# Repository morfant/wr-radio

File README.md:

# WR-Radio

## 설정 방법

### 1. 첫 실행
```bash
python3 wr-radio.py
```
첫 실행 시 `config.json` 파일이 자동 생성됩니다.

### 2. 스테이션 추가/변경
```bash
nano ~/wr-radio/config.json
```
```json
{
  "stations": [
    {
      "name": "내가 좋아하는 라디오",
      "url": "http://stream-url.mp3",
      "location": "Seoul, Korea",
      "lat": 37.5665,
      "lon": 126.9780,
      "color": [255, 100, 100]
    }
  ]
}
```

### 3. 날씨 기능 (선택)
1. https://openweathermap.org/appid 에서 무료 API 키 발급
2. `config.json`에 키 입력:
```json
   {
     "openweather_api_key": "여기에_키_입력"
   }
```

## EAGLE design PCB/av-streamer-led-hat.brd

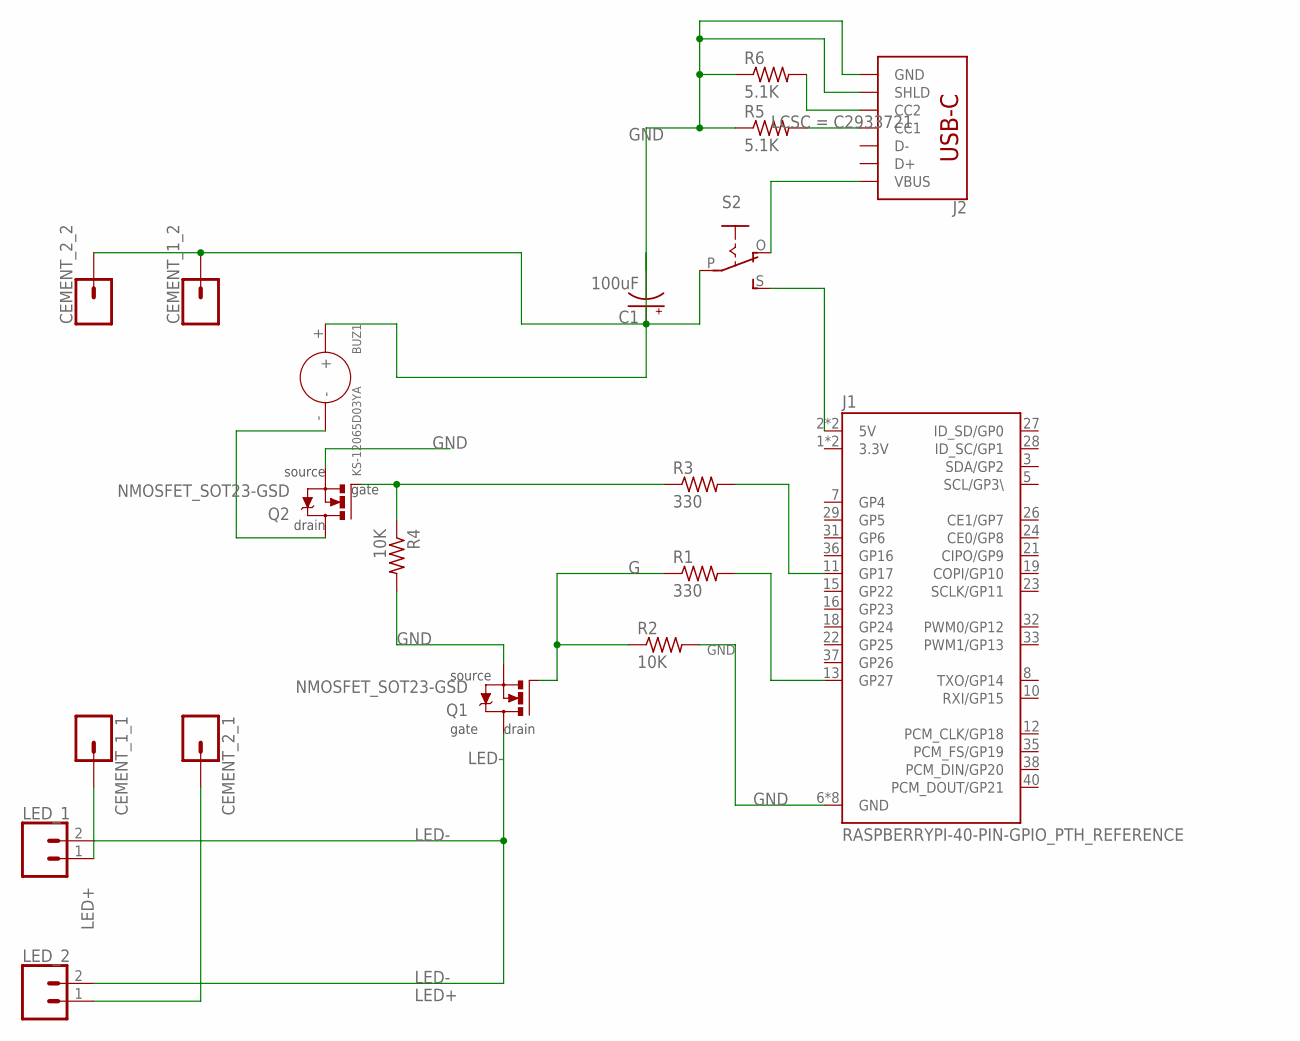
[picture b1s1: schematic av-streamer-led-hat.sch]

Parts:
BUZ1: KS-12065D03YA; BZ2-7.6-D12.0XH6.5MM
C1: 100uF; CPOL-RADIAL-2.5MM-6.5MM
CEMENT_1_1, CEMENT_1_2, CEMENT_2_1, CEMENT_2_2: CONN_01; 1X01
J1: RASPBERRYPI-40-PIN-GPIO_PTH_REFERENCE; RASPBERRY_PI_HAT_40_PIN_PTH_WITH_REFERNCE
J2: USB_C_2-LAYER_PADS; USB-C-16P-2LAYER-PADS
LED_1, LED_2: CONN_02; 1X02
Q1: NMOSFET_SOT23-GSD; SOT23; LCSC C181090
Q2: NMOSFET_SOT23-GSD; SOT23
R1, R3: 330; R1206
R2, R4: 10K; R1206
R5, R6: 5.1K; R1206; LCSC C2933721
S2: EG1218S; EG1218

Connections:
3.3V: J1.1 (3.3V), J1.17 (3.3V)
G: Q1.1 (G), R1.1, R2.1
GND: C1.2 (-), J1.6 (GND), J1.9 (GND), J1.14 (GND), J1.20 (GND), J1.25 (GND), J1.30 (GND), J1.34 (GND), J1.39 (GND), J2.GND, J2.GND2 (GND), J2.SHLD1 (SHLD), J2.SHLD2 (SHLD), J2.SHLD3 (SHLD), J2.SHLD4 (SHLD), Q1.2 (S), Q2.2 (S), R2.2, R4.2, R5.1, R6.1
LED+: CEMENT_1_1.1, CEMENT_2_1.1, LED_1.1, LED_2.1
LED-: LED_1.2, LED_2.2, Q1.3 (D)
unnamed: J1.11 (GP17), R3.2
unnamed: J1.13 (GP27), R1.2
unnamed: Q2.1 (G), R3.1, R4.1
unnamed: J2.A5 (CC1), R5.2
unnamed: J2.B5 (CC2), R6.2
unnamed: J2.VBUS1 (VBUS), J2.VBUS2 (VBUS), S2.O
unnamed: J1.2 (5V), J1.4 (5V), S2.S
unnamed: BUZ1.-, Q2.3 (D)
unnamed: BUZ1.+, C1.1 (+), CEMENT_1_2.1, CEMENT_2_2.1, S2.P

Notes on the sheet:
source
drain
gate

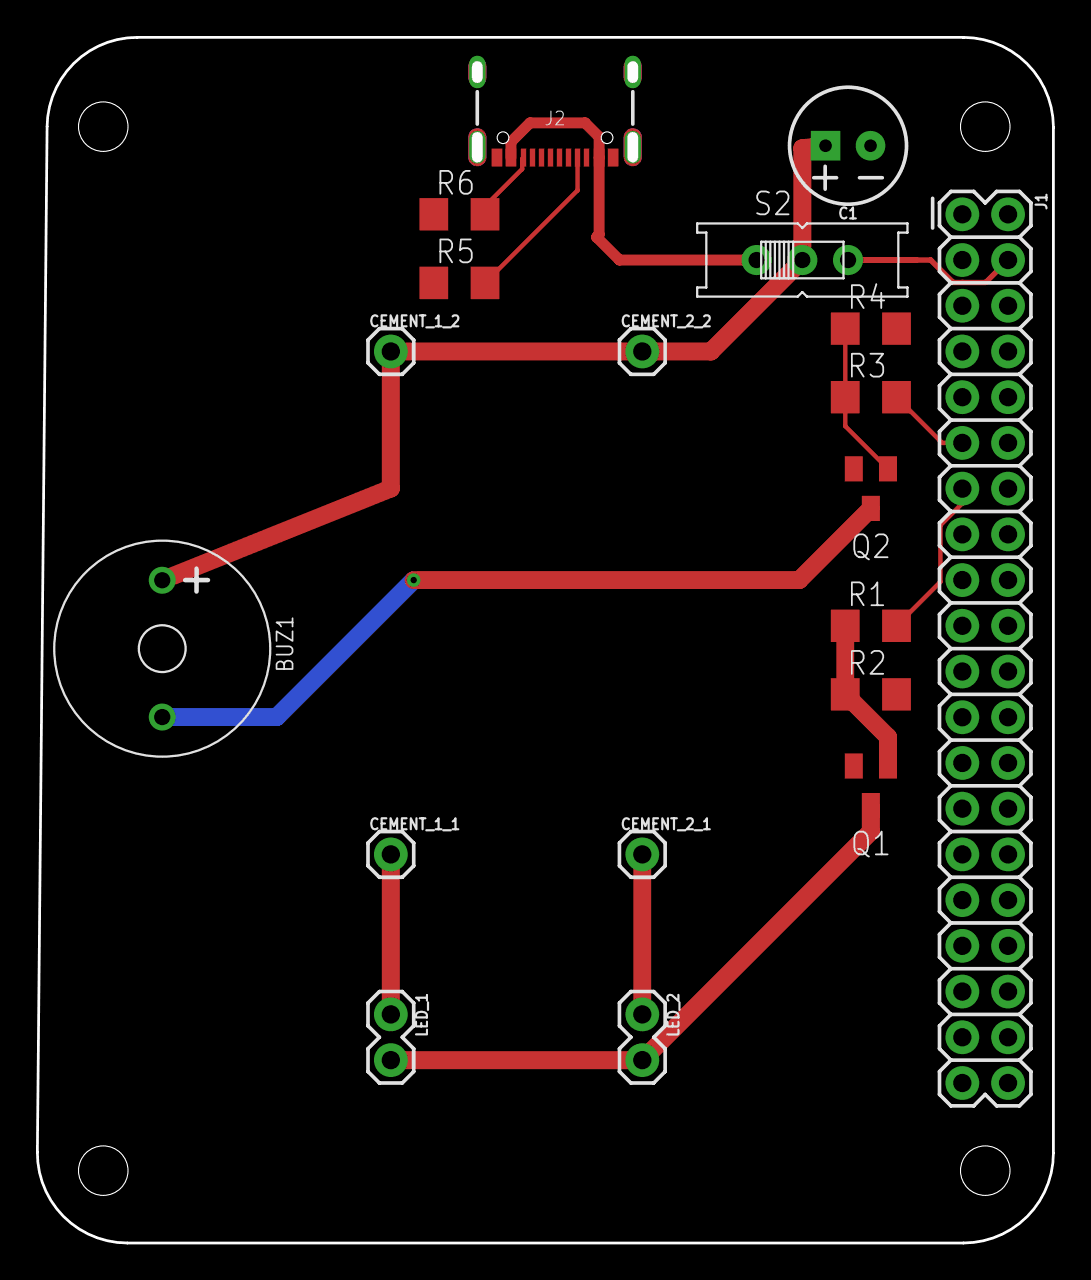
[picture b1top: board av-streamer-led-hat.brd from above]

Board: 2 copper layers, 56.4 x 67.0 mm, 19 parts (0 on the bottom side), 14 nets.

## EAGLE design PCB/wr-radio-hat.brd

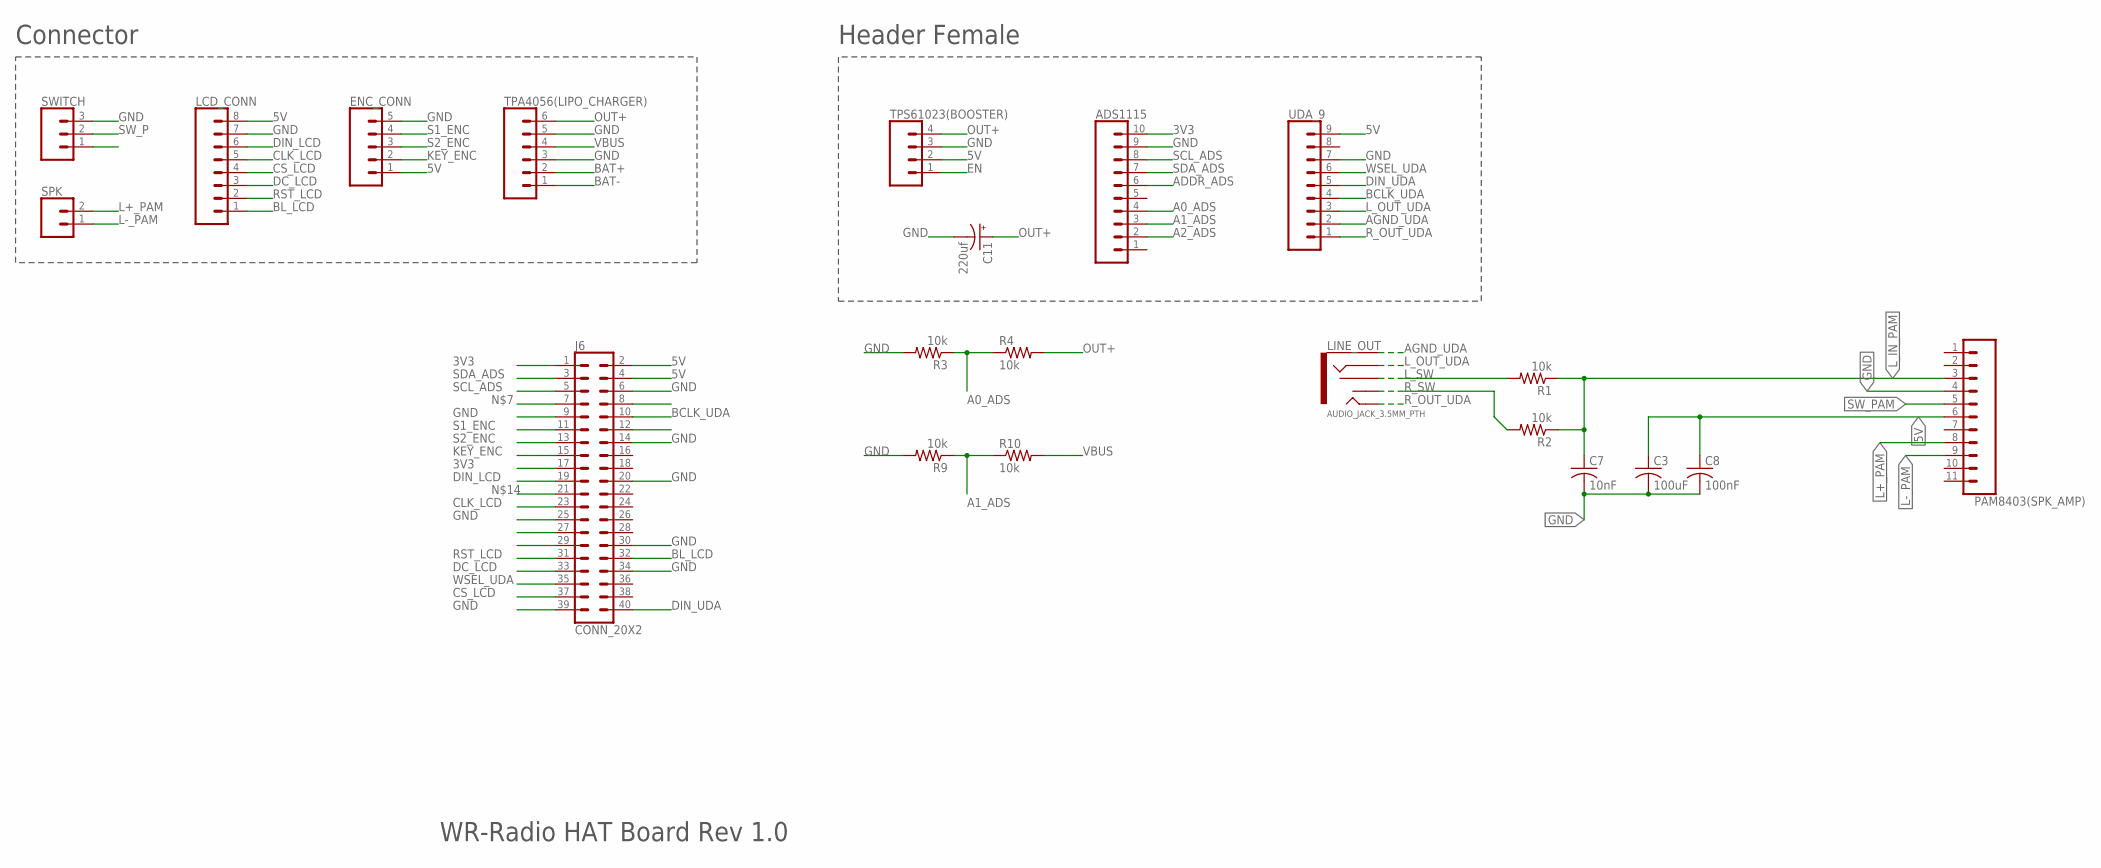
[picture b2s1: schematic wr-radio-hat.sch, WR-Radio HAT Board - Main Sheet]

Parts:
ADS1115: CONN_10"; 1X10
C3: 100uF; C050-050X075
C7: 10nF; C025-025X050
C8: 100nF; C025-025X050
C11: 220uf; E5-10,5
ENC_CONN: CONN_05PTH; 1X05
J6: CONN_20X2; 2X20
LCD_CONN: CONN_08"; 1X08
LINE_OUT: AUDIO_JACK_3.5MM_PTH; AUDIO-JACK
PAM8403(SPK_AMP): CONN_11_1.27MM; 1X11-1.27MM
R1, R2, R3, R4, R9, R10: 10k; 0207/10
SPK: CONN_02; 1X02
SWITCH: CONN_03; 1X03
TPA4056(LIPO_CHARGER): CONN_06SILK_FEMALE_PTH; 1X06
TPS61023(BOOSTER): CONN_04PTH; 1X04
UDA_9: CONN_09; 1X09

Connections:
3V3: ADS1115.10, J6.1, J6.17
5V: C3.1, C8.1, ENC_CONN.1, J6.2, J6.4, LCD_CONN.8 (VCC), PAM8403(SPK_AMP).6, TPS61023(BOOSTER).2, UDA_9.9
A0_ADS: ADS1115.4, R3.1, R4.1
A1_ADS: ADS1115.3, R9.1, R10.1
A2_ADS: ADS1115.2
ADDR_ADS: ADS1115.6
AGND_UDA: LINE_OUT.SLEEVE, UDA_9.2
BAT+: TPA4056(LIPO_CHARGER).2
BAT-: TPA4056(LIPO_CHARGER).1
BCLK_UDA: J6.10, UDA_9.4
BL_LCD: J6.32, LCD_CONN.1 (BL)
CLK_LCD: J6.23, LCD_CONN.5 (CLK)
CS_LCD: J6.37, LCD_CONN.4 (CS)
DC_LCD: J6.33, LCD_CONN.3 (DC)
DIN_LCD: J6.19, LCD_CONN.6 (DIN)
DIN_UDA: J6.40, UDA_9.5
EN: TPS61023(BOOSTER).1
GND: ADS1115.9, C3.2, C7.2, C8.2, C11.-, ENC_CONN.5, J6.6, J6.9, J6.14, J6.20, J6.25, J6.30, J6.34, J6.39, LCD_CONN.7 (GND), PAM8403(SPK_AMP).4, R3.2, R9.2, SWITCH.3, TPA4056(LIPO_CHARGER).3, TPA4056(LIPO_CHARGER).5, TPS61023(BOOSTER).3, UDA_9.7
KEY_ENC: ENC_CONN.2, J6.15
L+_PAM: PAM8403(SPK_AMP).8, SPK.2
L-_PAM: PAM8403(SPK_AMP).9, SPK.1
L_IN_PAM: C7.1, PAM8403(SPK_AMP).3, R1.1, R2.1
L_OUT_UDA: LINE_OUT.RING, UDA_9.3
L_SW: LINE_OUT.RSH, R1.2
OUT+: C11.+, R4.2, TPA4056(LIPO_CHARGER).6, TPS61023(BOOSTER).4
RST_LCD: J6.31, LCD_CONN.2 (RST)
R_OUT_UDA: LINE_OUT.TIP, UDA_9.1
R_SW: LINE_OUT.TSH, R2.2
S1_ENC: ENC_CONN.4, J6.11
S2_ENC: ENC_CONN.3, J6.13
SCL_ADS: ADS1115.8, J6.5
SDA_ADS: ADS1115.7, J6.3
SW_P: SWITCH.2
SW_PAM: PAM8403(SPK_AMP).5
VBUS: R10.2, TPA4056(LIPO_CHARGER).4
WSEL_UDA: J6.35, UDA_9.6

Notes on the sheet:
WR-Radio HAT Board Rev 1.0
Connector
Header Female

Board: 2 copper layers, 21 parts (0 on the bottom side), 29 nets, no tracks yet.

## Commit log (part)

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2026-02-02 Edit run_radio.py
2026-02-13 add lcd_test.py
2026-02-13 Add main.py
2026-02-15 edit encoder pin out
2026-02-15 Edit main.py
2026-02-15 oled test
2026-02-15 Change file name
2026-02-15 Add README, add weathre infomation
2026-02-15 Add .gitignore and config.json.example
2026-02-16 Display update, Seperate files
2026-02-16 Remove __pycache__ and pyc files
2026-02-16 Edit .gitignore
2026-02-17 Save volume and backlight. Change way to enter blt mode
2026-02-18 Loading animation
2026-02-18 Display UTC time
2026-02-18 Vol 100% display OK
2026-02-20 LCD pin change
2026-02-20 Use audio
2026-02-25 Edit EQ, Add bat_test.py
2026-02-25 Display battery status, Fix weather update timing
2026-02-25 Weather display init time change
2026-02-26 Earphone insert check system
2026-02-28 Pam 모듈 교체 후 음량 테스트
2026-02-28 Edit player.py
2026-02-28 Add some tesets
2026-02-28 Max volume = 150
2026-02-28 LCD SPI update interval change (1.0)
2026-03-02 Fix pin numbers on lcd_test.py
2026-03-02 Add boot_greeting.py
2026-03-04 Add system setting menu with long press
2026-03-04 Menu 정리
2026-03-04 첫 시작시 배터리 측정 오류 수정
2026-03-04 Edit exit message
2026-03-04 Edit shutting down message
2026-03-06 Add BT test
2026-03-06 BT 기본 기능 구현
2026-03-06 BT 기능 개선
2026-03-07 BT scan 기능 확인
2026-04-02 Add PCB files
2026-04-30 PCB v0.5 수정 후 작동 확인, note 업데이트
2026-06-29 Case modeling

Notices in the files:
parts and their libraries:
SparkFun-Connectors: Licensing: Creative Commons ShareAlike 4.0 International - https://creativecommons.org/licenses/by-sa/4.0
